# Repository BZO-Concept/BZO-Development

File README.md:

# BZO Concept – Development

Development boards and libraries designed by **BZO Concept** to test circuits in real conditions.
These boards are used during development and are shared, complete and working, so anyone can study, build or reuse them.
This repository mirrors the *Développement* section of [bzo-concept.fr](https://www.bzo-concept.fr/developpement/).

## Boards (KiCad projects, PDF schematics, production files)

| Folder | Description |
|---|---|
| [UART_UPDI_Dongle](UART_UPDI_Dongle) | USB–UART / UPDI dongle for programming and debugging, with quick access to 5V, 3V3 and GND rails |
| [AVR32DD32_DevBoard](AVR32DD32_DevBoard) | Nano-sized AVR32DD32 board: 24 MHz internal oscillator, 23 ADCs, DAC, MVIO. Arduino IDE + [DxCore](https://github.com/SpenceKonde/DxCore) |
| [BigBoard_STM32F405](BigBoard_STM32F405) | Large STM32F405RGT6 test board: every useful pin on headers with LED drivers. Used to validate pin assignment, serial, CAN and firmware on BZO ECUs. Arduino IDE + [Arduino Core STM32](https://github.com/stm32duino/Arduino_Core_STM32) |
| [STM32F042F6P7_DevBoard](STM32F042F6P7_DevBoard) | Small STM32F042F6P7 (TSSOP-20, 48 MHz) board with USB–UART, programmable from Arduino IDE. Arduino IDE + [Arduino Core STM32](https://github.com/stm32duino/Arduino_Core_STM32) |

## Libraries (Arduino IDE)

| Folder | Description |
|---|---|
| [BZO_PWM_Generator](BZO_PWM_Generator) | Software PWM on any pin of any processor (ATtiny, ATmega, STM32…), 1–1000 Hz, duty or frequency modulation, 4 independent channels, no dependency |
| [TunerStudio_Library](TunerStudio_Library) | Universal TunerStudio communication library (and any `.ini` based software) for configuration and monitoring of custom modules. Bluetooth tested (MSDroid). Example sketch and `.ini` included |

## See also

ECU firmware, datasheets and tools: [BZO-Downloads](https://github.com/BZO-Concept/BZO-Downloads)

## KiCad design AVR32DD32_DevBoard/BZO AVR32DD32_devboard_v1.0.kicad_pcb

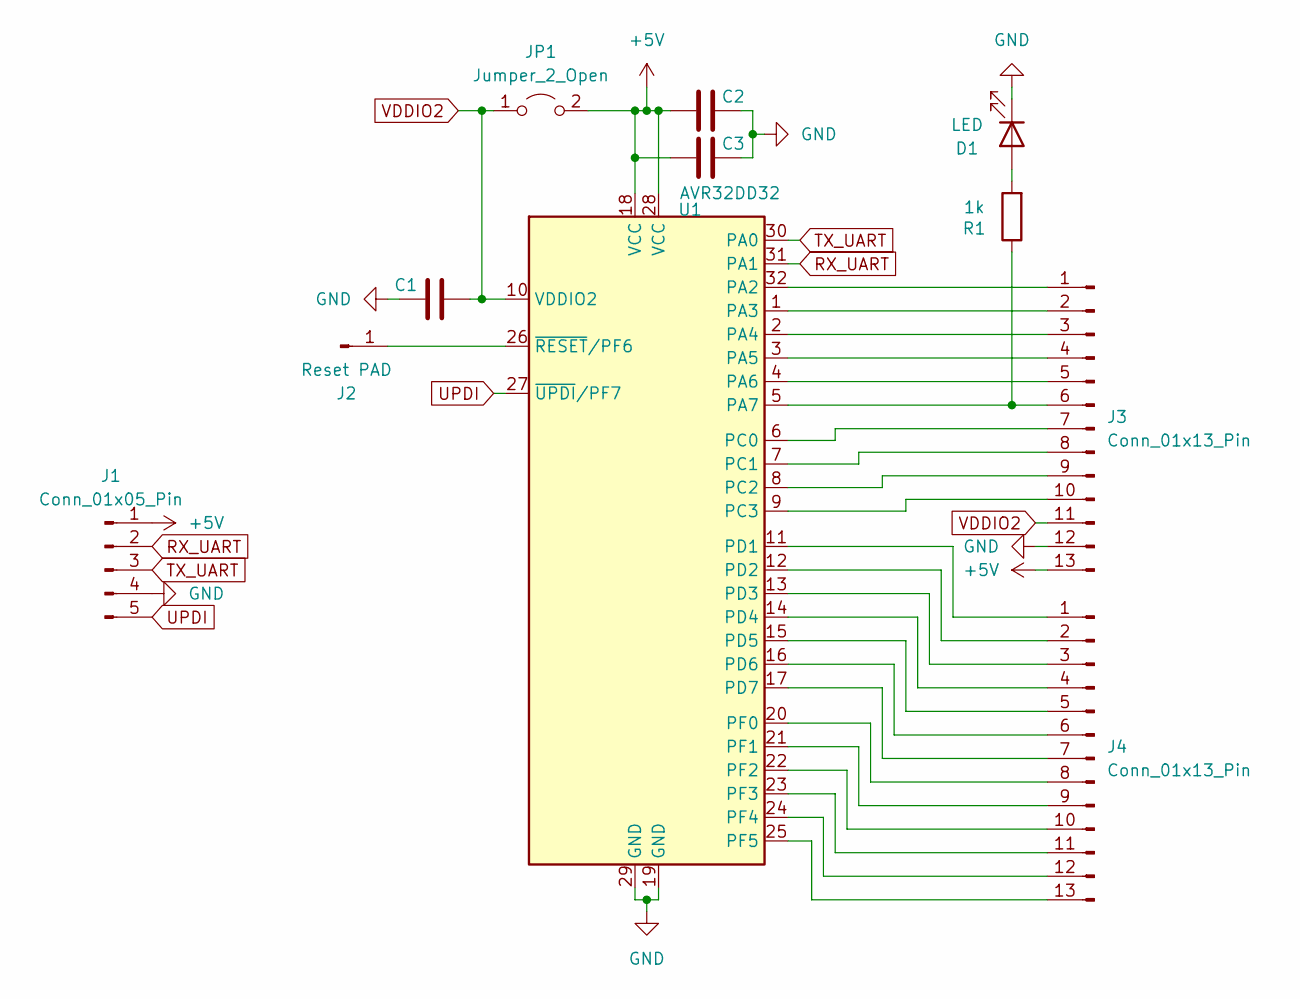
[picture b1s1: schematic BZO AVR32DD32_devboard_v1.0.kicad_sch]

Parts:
C1, C2, C3: 0.1uF; C_0805_2012Metric_Pad1.18x1.45mm_HandSolder; LCSC Part # C0805C104J5RACTU
D1: LED; LED_1206_3216Metric_Pad1.42x1.75mm_HandSolder(clean); LCSC Part # //////////////////////////
J1: Conn_01x05_Pin; PinHeader_1x05_P2.54mm_Vertical; LCSC Part # //////////////////////////
J2: Reset PAD; PinHeader_1x01_P1.00mm_Vertical; LCSC Part # //////////////////////////
J3, J4: Conn_01x13_Pin; PinHeader_1x13_P2.54mm_Vertical; LCSC Part # //////////////////////////
JP1: Jumper_2_Open; SolderJumper-2_P1.3mm_Open_RoundedPad1.0x1.5mm; LCSC Part # //////////////////////////
R1: 1k; R_0805_2012Metric_Pad1.20x1.40mm_HandSolder; LCSC Part # CR0805-FX-1001ELF
U1: AVR32DD32; TQFP-32_7x7mm_P0.8mm; LCSC Part # AVR32DD32

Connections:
+5V: C2.1, C3.1, J1.1, J3.13, JP1.2 (B), U1.18 (VCC), U1.28 (VCC)
GND: C1.1, C2.2, C3.2, D1.1 (K), J1.4, J3.12, U1.19 (GND), U1.29 (GND)
unnamed: D1.2 (A), R1.2
unnamed: J2.1, U1.26 (~RESET/PF6)
unnamed: J3.1, U1.32 (PA2)
unnamed: J3.2, U1.1 (PA3)
unnamed: J3.3, U1.2 (PA4)
unnamed: J3.4, U1.3 (PA5)
unnamed: J3.5, U1.4 (PA6)
unnamed: J3.6, R1.1, U1.5 (PA7)
unnamed: J3.7, U1.6 (PC0)
unnamed: J3.8, U1.7 (PC1)
unnamed: J3.9, U1.8 (PC2)
unnamed: J3.10, U1.9 (PC3)
unnamed: J4.1, U1.11 (PD1)
unnamed: J4.2, U1.12 (PD2)
unnamed: J4.3, U1.13 (PD3)
unnamed: J4.4, U1.14 (PD4)
unnamed: J4.5, U1.15 (PD5)
unnamed: J4.6, U1.16 (PD6)
unnamed: J4.7, U1.17 (PD7)
unnamed: J4.8, U1.20 (PF0)
unnamed: J4.9, U1.21 (PF1)
unnamed: J4.10, U1.22 (PF2)
unnamed: J4.11, U1.23 (PF3)
unnamed: J4.12, U1.24 (PF4)
unnamed: J4.13, U1.25 (PF5)
RX_UART: J1.2, U1.31 (PA1)
TX_UART: J1.3, U1.30 (PA0)
UPDI: J1.5, U1.27 (~UPDI/PF7)
VDDIO2: C1.2, J3.11, JP1.1 (A), U1.10 (VDDIO2)

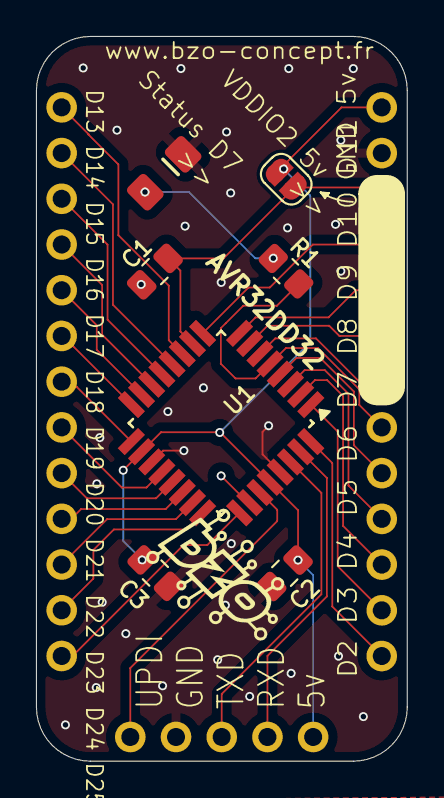
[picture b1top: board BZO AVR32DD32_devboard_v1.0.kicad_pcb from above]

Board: 2 copper layers, 20.6 x 40.3 mm, 11 parts (1 on the bottom side), 31 nets.

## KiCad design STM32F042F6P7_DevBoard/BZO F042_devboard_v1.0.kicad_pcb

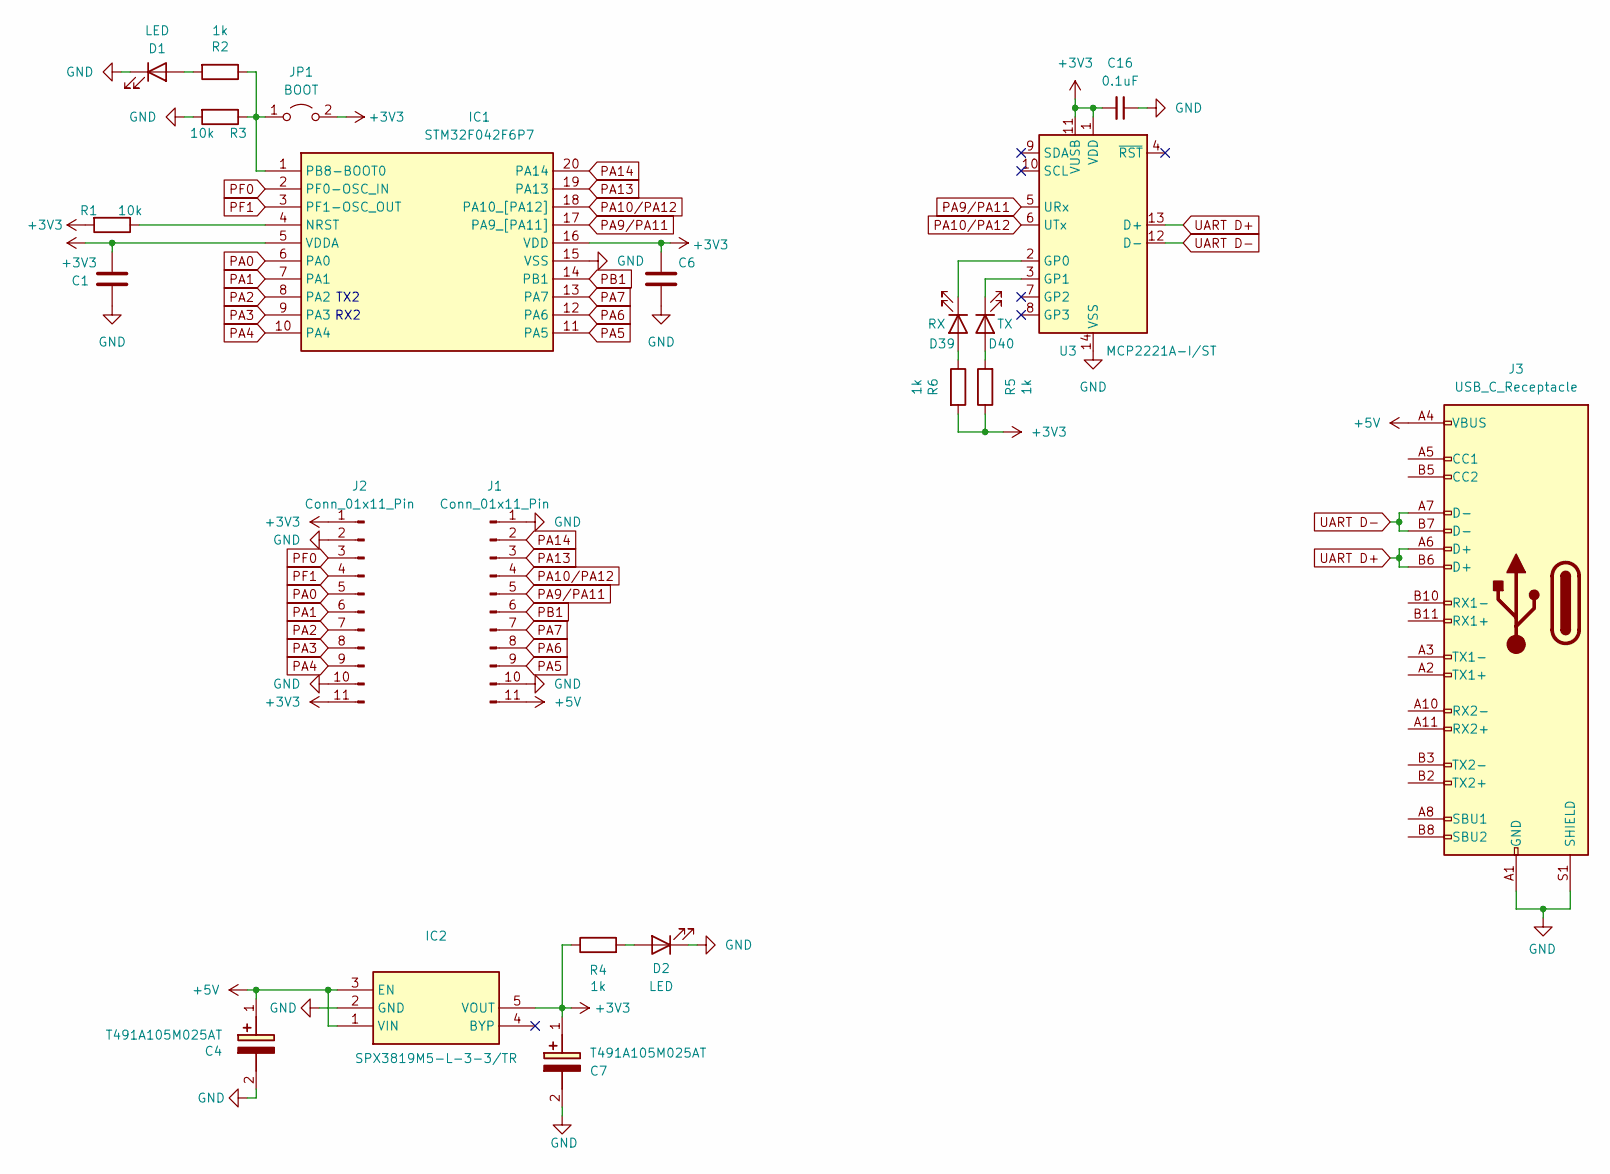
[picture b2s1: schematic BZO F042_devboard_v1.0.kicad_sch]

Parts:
C1, C6, C16: 0.1uF; C_0805_2012Metric_Pad1.18x1.45mm_HandSolder; LCSC Part # C0805C104J5RACTU
C4, C7: T491A105M025AT; T491A(clean); Mouser Part Number 80-T491A105M025
D1, D2: LED; LED_1206_3216Metric_Pad1.42x1.75mm_HandSolder(clean); LCSC Part # //////////////////////////
D39: RX; LED_1206_3216Metric_Pad1.42x1.75mm_HandSolder(clean); LCSC Part # //////////////////////////
D40: TX; LED_1206_3216Metric_Pad1.42x1.75mm_HandSolder(clean); LCSC Part # //////////////////////////
IC1: STM32F042F6P7; CLT34BT6; Mouser Part Number 511-STM32F042F6P7
IC2: SPX3819M5-L-3-3/TR; SOT95P280X145-5N; Mouser Part Number 701-SPX3819M5-L-50TR
J1, J2: Conn_01x11_Pin; PinHeader_1x11_P2.54mm_Vertical
J3: USB_C_Receptacle; USB_C_Receptacle_GCT_USB4085; LCSC Part # USB4085-GF-A
JP1: BOOT; SW_Push_SPST_NO_Alps_SKRK
R1, R3: 10k; R_0805_2012Metric_Pad1.20x1.40mm_HandSolder; LCSC Part # CR0805-FX-1002ELF
R2, R4, R5, R6: 1k; R_0805_2012Metric_Pad1.20x1.40mm_HandSolder; LCSC Part # CR0805-FX-1001ELF
U3: MCP2221A-I/ST; TSSOP-14_4.4x5mm_P0.65mm; LCSC Part # MCP2221A-I/ST

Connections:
+3V3: C1.1, C6.1, C7.1 (+), C16.2, IC1.5 (VDDA), IC1.16 (VDD), IC2.5 (VOUT), J2.1, J2.11, JP1.2 (B), R1.2, R4.1, R5.1, R6.2, U3.1 (VDD), U3.11 (VUSB)
+5V: C4.1 (+), IC2.1 (VIN), IC2.3 (EN), J1.11, J3.A4 (VBUS), J3.A9 (VBUS), J3.B4 (VBUS), J3.B9 (VBUS)
GND: C1.2, C4.2 (-), C6.2, C7.2 (-), C16.1, D1.1 (K), D2.1 (K), IC1.15 (VSS), IC2.2 (GND), J1.1, J1.10, J2.2, J2.10, J3.A1 (GND), J3.A12 (GND), J3.B1 (GND), J3.B12 (GND), J3.S1 (SHIELD), R3.2, U3.14 (VSS)
unnamed: D1.2 (A), R2.2
unnamed: D2.2 (A), R4.2
unnamed: D39.2 (A), R6.1
unnamed: D39.1 (K), U3.2 (GP0)
unnamed: D40.2 (A), R5.2
unnamed: D40.1 (K), U3.3 (GP1)
unnamed: IC1.4 (NRST), R1.1
unnamed: IC1.1 (PB8-BOOT0), JP1.1 (A), R2.1, R3.1
PA0: IC1.6 (PA0), J2.5
PA1: IC1.7 (PA1), J2.6
PA2: IC1.8 (PA2), J2.7
PA3: IC1.9 (PA3), J2.8
PA4: IC1.10 (PA4), J2.9
PA5: IC1.11 (PA5), J1.9
PA6: IC1.12 (PA6), J1.8
PA7: IC1.13 (PA7), J1.7
PA9/PA11: IC1.17 (PA9_[PA11]), J1.5, U3.5 (URx)
PA10/PA12: IC1.18 (PA10_[PA12]), J1.4, U3.6 (UTx)
PA13: IC1.19 (PA13), J1.3
PA14: IC1.20 (PA14), J1.2
PB1: IC1.14 (PB1), J1.6
PF0: IC1.2 (PF0-OSC_IN), J2.3
PF1: IC1.3 (PF1-OSC_OUT), J2.4
UART D+: J3.A6 (D+), J3.B6 (D+), U3.13 (D+)
UART D-: J3.A7 (D-), J3.B7 (D-), U3.12 (D-)

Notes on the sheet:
TX2
RX2

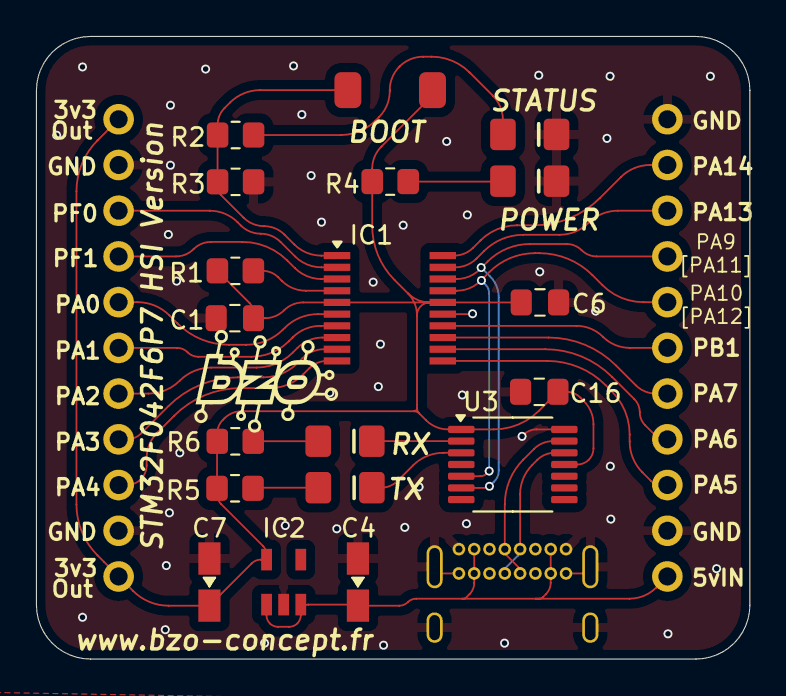
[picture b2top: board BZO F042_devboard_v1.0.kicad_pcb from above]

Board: 2 copper layers, 39.6 x 34.6 mm, 22 parts (0 on the bottom side), 28 nets.

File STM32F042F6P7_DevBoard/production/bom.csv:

Designator,Footprint,Quantity,Value,LCSC Part #
"C1, C16, C6",0805,3,0.1uF,C0805C104J5RACTU
"C4, C7",T491A(clean),2,T491A105M025AT,
"D1, D2",1206,2,LED,//////////////////////////
D39,1206,1,RX,//////////////////////////
D40,1206,1,TX,//////////////////////////
IC1,CLT34BT6,1,STM32F042F6P7,
IC2,SOT95P280X145-5N,1,SPX3819M5-L-3-3/TR,
"J1, J2",PinHeader_1x11_P2.54mm_Vertical,2,Conn_01x11_Pin,
J3,USB_C_Receptacle_GCT_USB4085,1,USB_C_Receptacle,USB4085-GF-A
JP1,SW_Push_SPST_NO_Alps_SKRK,1,BOOT,
"R1, R3",0805,2,10k,CR0805-FX-1002ELF
"R2, R4, R5, R6",0805,4,1k,CR0805-FX-1001ELF
U3,TSSOP-14_4.4x5mm_P0.65mm,1,MCP2221A-I/ST,MCP2221A-I/ST

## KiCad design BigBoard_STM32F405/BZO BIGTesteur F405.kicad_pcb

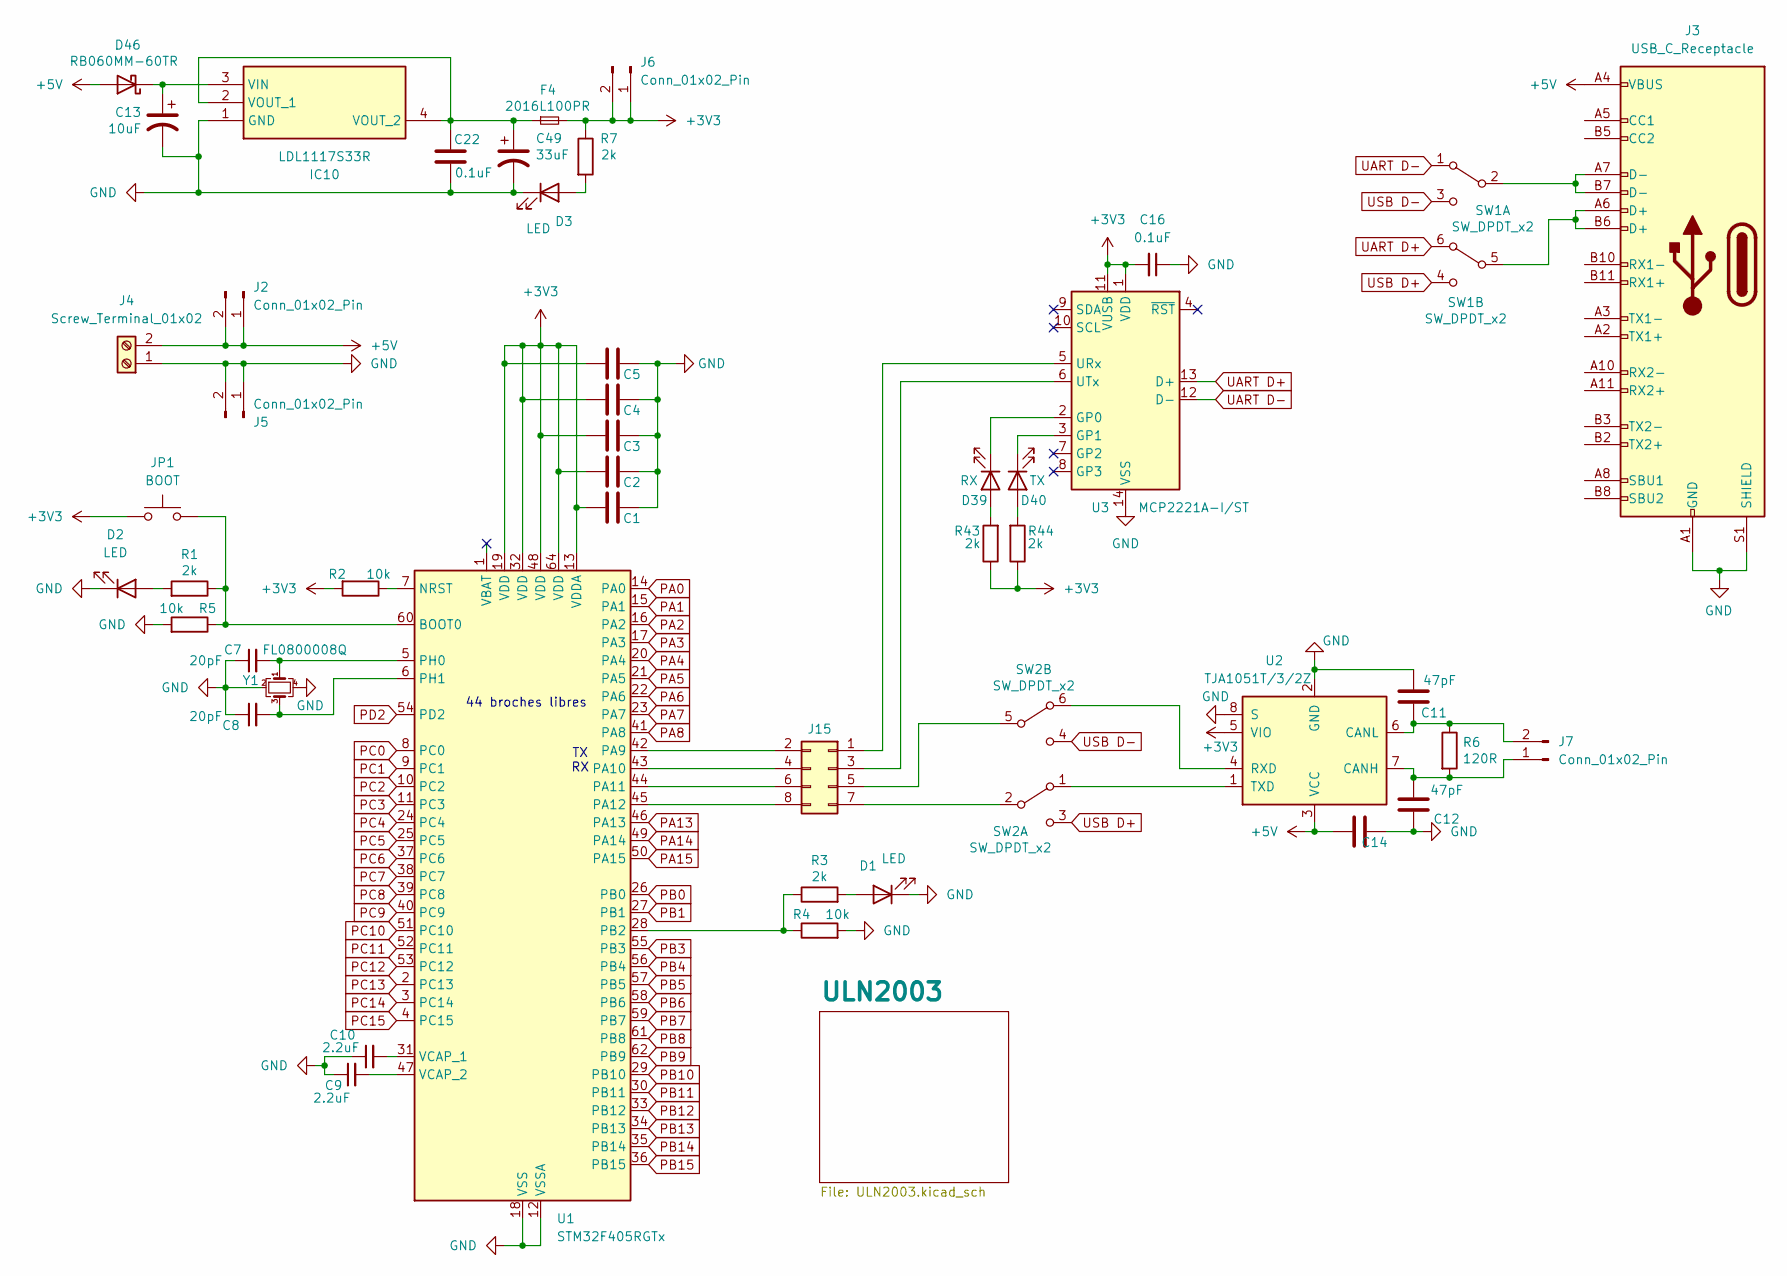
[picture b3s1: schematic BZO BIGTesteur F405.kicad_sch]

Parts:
C1, C2, C3, C4, C5, C14, C16, C22: 0.1uF; C_0805_2012Metric_Pad1.18x1.45mm_HandSolder; LCSC Part # C0805C104J5RACTU
C7, C8: 20pF; C_0805_2012Metric_Pad1.18x1.45mm_HandSolder; LCSC Part # C0805C200J5HACTU
C9, C10: 2.2uF; C_0805_2012Metric_Pad1.18x1.45mm_HandSolder; LCSC Part # C0805C225J4REC7210
C11, C12: 47pF; C_0805_2012Metric_Pad1.18x1.45mm_HandSolder; LCSC Part # C0805C470J5GACTU
C13: 10uF; CP_EIA-6032-28_Kemet-C_Pad2.25x2.35mm_HandSolder; LCSC Part # T491C106K035ATAUTO
C49: 33uF; CP_EIA-3528-21_Kemet-B_Pad1.50x2.35mm_HandSolder; LCSC Part # T491B336K016ATAUTO
D1, D2, D3: LED; LED_1206_3216Metric_ReverseMount; LCSC Part # //////////////////////////
D39: RX; LED_1206_3216Metric_ReverseMount; LCSC Part # //////////////////////////
D40: TX; LED_1206_3216Metric_ReverseMount; LCSC Part # //////////////////////////
D46: RB060MM-60TR; LED_1206_3216Metric_Pad1.42x1.75mm_HandSolder(clean); Mouser Part Number 755-RB060MM-60TR
F4: 2016L100PR; FUSC5141X160N; LCSC Part # 2016L100PR
IC10: LDL1117S33R; SOT230P700X180-4N; Mouser Part Number 511-LDL1117S33R
J2, J5, J6, J7: Conn_01x02_Pin; PinHeader_2x01_P2.54mm_Vertical; LCSC Part # //////////////////////////
J3: USB_C_Receptacle; USB_C_Receptacle_GCT_USB4085; LCSC Part # USB4085-GF-A
J4: Screw_Terminal_01x02; TerminalBlock_bornier-2_P5.08mm; LCSC Part # //////////////////////////
J15: Conn_02x04_Counter_Clockwise; PinHeader_2x04_P2.54mm_Vertical; LCSC Part # //////////////////////////
JP1: BOOT; SW_Push_SPST_NO_Alps_SKRK; LCSC Part # //////////////////////////
R1, R3, R7, R43, R44: 2k; R_0805_2012Metric_Pad1.20x1.40mm_HandSolder; LCSC Part # CR0805-FX-2001ELF
R2, R4, R5: 10k; R_0805_2012Metric_Pad1.20x1.40mm_HandSolder; LCSC Part # CR0805-FX-1002ELF
R6: 120R; R_0805_2012Metric_Pad1.20x1.40mm_HandSolder; LCSC Part # CR0805-FX-1200ELF
SW1, SW2: SW_DPDT_x2; SMDIP-6_W7.62mm; LCSC Part # //////////////////////////
U1: STM32F405RGTx; LQFP-64_10x10mm_P0.5mm; LCSC Part # STM32F405RGTx
U2: TJA1051T/3/2Z; SOIC-8_3.9x4.9mm_P1.27mm; LCSC Part # TJA1051T/3/2Z
U3: MCP2221A-I/ST; TSSOP-14_4.4x5mm_P0.65mm; LCSC Part # MCP2221A-I/ST
Y1: FL0800008Q; Mouser Part Number 729-FL0800008Q

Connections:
+3V3: C1.1, C2.1, C3.1, C4.1, C5.1, C16.2, F4.2, J6.1, J6.2, JP1.1, R2.2, R7.1, R43.1, R44.1, U1.13 (VDDA), U1.19 (VDD), U1.32 (VDD), U1.48 (VDD), U1.64 (VDD), U2.5 (VIO), U3.1 (VDD), U3.11 (VUSB); also elsewhere on the board
+5V: C14.1, D46.2 (A), J2.1, J2.2, J3.A4 (VBUS), J3.A9 (VBUS), J3.B4 (VBUS), J3.B9 (VBUS), J4.2, U2.3 (VCC)
GND: C1.2, C2.2, C3.2, C4.2, C5.2, C7.1, C8.1, C9.1, C10.1, C11.1, C12.2, C13.2, C14.2, C16.1, C22.2, C49.2, D1.1 (K), D2.1 (K), D3.1 (K), IC10.1 (GND), J3.A1 (GND), J3.A12 (GND), J3.B1 (GND), J3.B12 (GND), J3.S1 (SHIELD), J4.1, J5.1, J5.2, R4.2, R5.2, U1.12 (VSSA), U1.18 (VSS), U1.63 (VSS), U2.2 (GND), U2.8 (S), U3.14 (VSS), Y1.2, Y1.4; also elsewhere on the board
unnamed: D1.2 (A), R3.2
unnamed: D2.2 (A), R1.2
unnamed: D3.2 (A), R7.2
unnamed: D39.2 (A), R43.2
unnamed: D39.1 (K), U3.2 (GP0)
unnamed: D40.2 (A), R44.2
unnamed: D40.1 (K), U3.3 (GP1)
unnamed: C13.1, D46.1 (K), IC10.3 (VIN)
unnamed: C22.1, C49.1, F4.1, IC10.2 (VOUT_1), IC10.4 (VOUT_2)
unnamed: C12.1, J7.1, R6.2, U2.7 (CANH)
unnamed: C11.2, J7.2, R6.1, U2.6 (CANL)
unnamed: J15.1, U3.5 (URx)
unnamed: J15.2, U1.42 (PA9)
unnamed: J15.3, U3.6 (UTx)
unnamed: J15.4, U1.43 (PA10)
unnamed: J15.5, SW2.5 (B)
unnamed: J15.6, U1.44 (PA11)
unnamed: J15.7, SW2.2 (B)
unnamed: J15.8, U1.45 (PA12)
unnamed: J3.A7 (D-), J3.B7 (D-), SW1.2 (B)
unnamed: J3.A6 (D+), J3.B6 (D+), SW1.5 (B)
unnamed: SW2.1 (A), U2.1 (TXD)
unnamed: SW2.6 (A), U2.4 (RXD)
unnamed: JP1.2, R1.1, R5.1, U1.60 (BOOT0)
unnamed: R2.1, U1.7 (NRST)
unnamed: R3.1, R4.1, U1.28 (PB2)
unnamed: C7.2, U1.5 (PH0), Y1.1
unnamed: C8.2, U1.6 (PH1), Y1.3
unnamed: C10.2, U1.31 (VCAP_1)
unnamed: C9.2, U1.47 (VCAP_2)
PA0: U1.14 (PA0); also elsewhere on the board
PA1: U1.15 (PA1); also elsewhere on the board
PA2: U1.16 (PA2); also elsewhere on the board
PA3: U1.17 (PA3); also elsewhere on the board
PA4: U1.20 (PA4); also elsewhere on the board
PA5: U1.21 (PA5); also elsewhere on the board
PA6: U1.22 (PA6); also elsewhere on the board
PA7: U1.23 (PA7); also elsewhere on the board
PA8: U1.41 (PA8); also elsewhere on the board
PA13: U1.46 (PA13); also elsewhere on the board
PA14: U1.49 (PA14); also elsewhere on the board
PA15: U1.50 (PA15); also elsewhere on the board
PB0: U1.26 (PB0); also elsewhere on the board
PB1: U1.27 (PB1); also elsewhere on the board
PB3: U1.55 (PB3); also elsewhere on the board
PB4: U1.56 (PB4); also elsewhere on the board
PB5: U1.57 (PB5); also elsewhere on the board
PB6: U1.58 (PB6); also elsewhere on the board
PB7: U1.59 (PB7); also elsewhere on the board
PB8: U1.61 (PB8); also elsewhere on the board
PB9: U1.62 (PB9); also elsewhere on the board
PB10: U1.29 (PB10); also elsewhere on the board
PB11: U1.30 (PB11); also elsewhere on the board
PB12: U1.33 (PB12); also elsewhere on the board
PB13: U1.34 (PB13); also elsewhere on the board
PB14: U1.35 (PB14); also elsewhere on the board
PB15: U1.36 (PB15); also elsewhere on the board
PC0: U1.8 (PC0); also elsewhere on the board
PC1: U1.9 (PC1); also elsewhere on the board
PC2: U1.10 (PC2); also elsewhere on the board
PC3: U1.11 (PC3); also elsewhere on the board
PC4: U1.24 (PC4); also elsewhere on the board
PC5: U1.25 (PC5); also elsewhere on the board
PC6: U1.37 (PC6); also elsewhere on the board
PC7: U1.38 (PC7); also elsewhere on the board
PC8: U1.39 (PC8); also elsewhere on the board
PC9: U1.40 (PC9); also elsewhere on the board
PC10: U1.51 (PC10); also elsewhere on the board
PC11: U1.52 (PC11); also elsewhere on the board
PC12: U1.53 (PC12); also elsewhere on the board
PC13: U1.2 (PC13); also elsewhere on the board
PC14: U1.3 (PC14); also elsewhere on the board
PC15: U1.4 (PC15); also elsewhere on the board
PD2: U1.54 (PD2); also elsewhere on the board
UART D+: SW1.6 (A), U3.13 (D+)
UART D-: SW1.1 (A), U3.12 (D-)
USB D+: SW1.4 (C), SW2.3 (C)
USB D-: SW1.3 (C), SW2.4 (C)

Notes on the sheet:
TX RX
44 broches libres

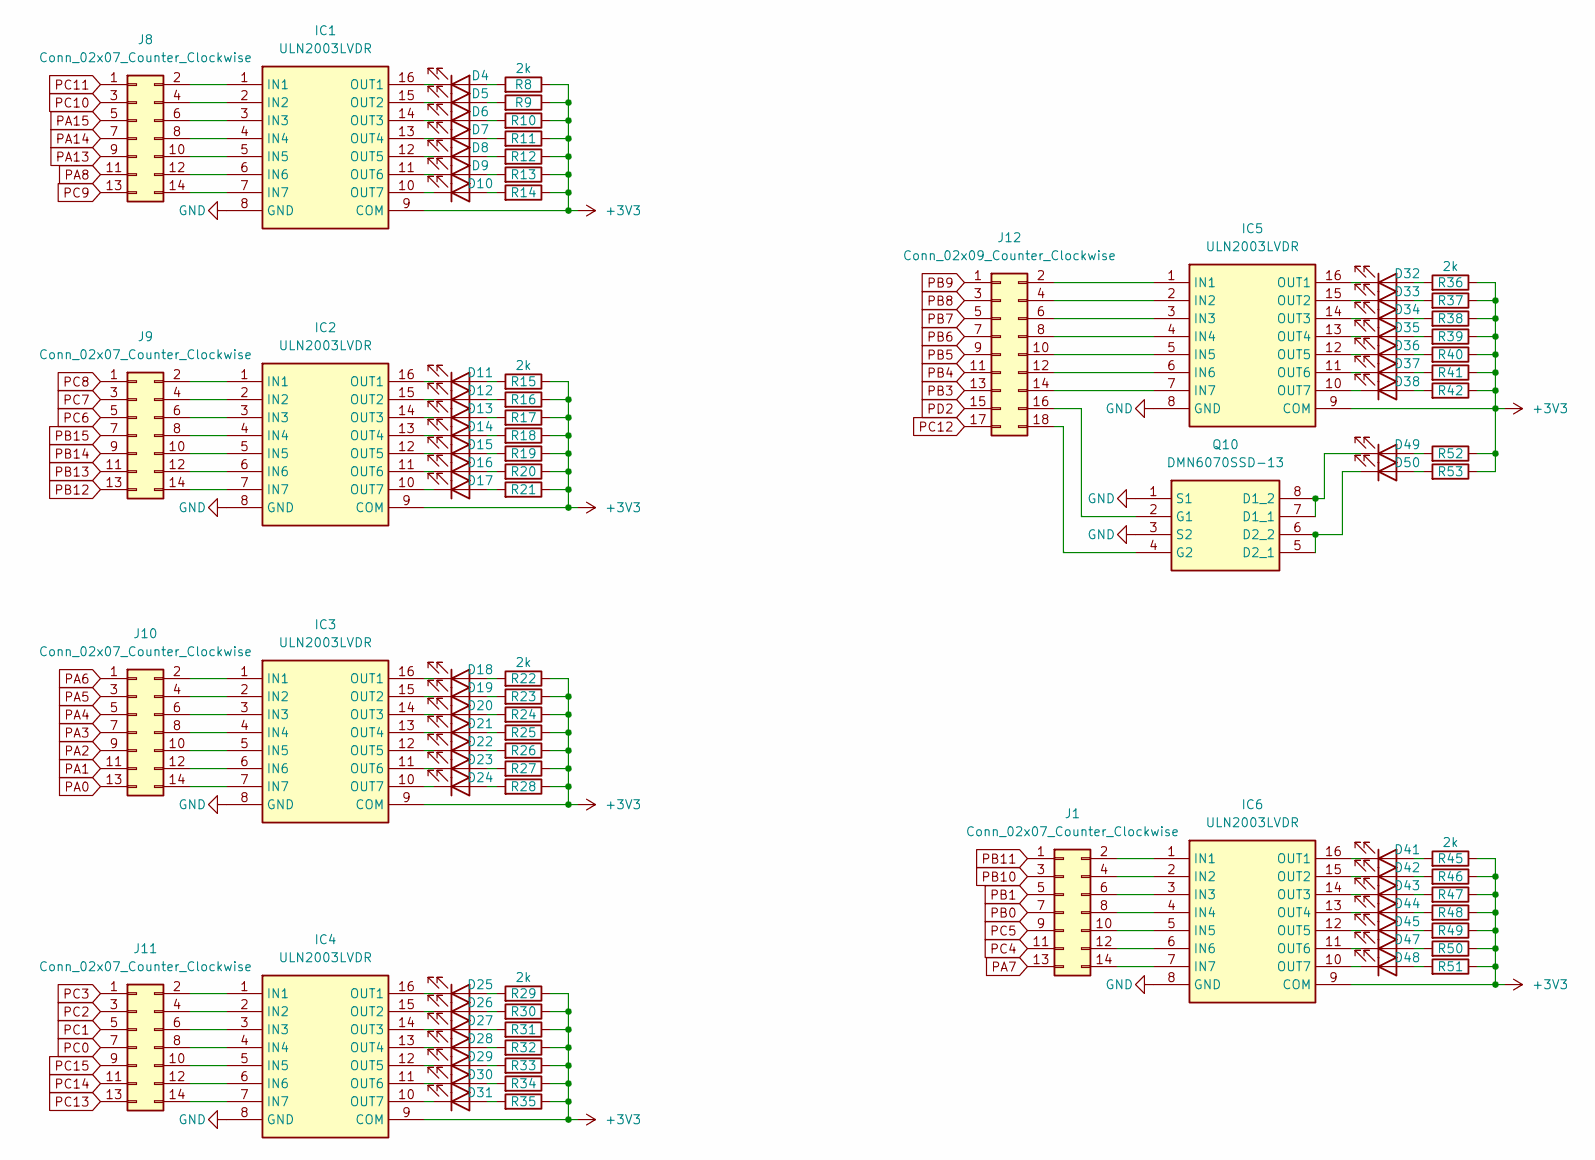
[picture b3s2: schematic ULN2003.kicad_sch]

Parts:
D4, D5, D6, D7, D8, D9, D10, D11, D12, D13, D14, D15, D16, D17, D18, D19, D20, D21, D22, D23, D24, D25, D26, D27, D28, D29, D30, D31, D32, D33, D34, D35, D36, D37, D38, D41, D42, D43, D44, D45, D47, D48, D49, D50: LED; LED_1206_3216Metric_ReverseMount; LCSC Part # //////////////////////////
IC1, IC2, IC3, IC4, IC5, IC6: ULN2003LVDR; SOIC127P600X175-16N; Mouser Part Number 595-ULN2003LVDR
J1, J8, J9, J10, J11: Conn_02x07_Counter_Clockwise; PinHeader_2x07_P2.54mm_Vertical; LCSC Part # //////////////////////////
J12: Conn_02x09_Counter_Clockwise; PinHeader_2x09_P2.54mm_Vertical; LCSC Part # //////////////////////////
Q10: DMN6070SSD-13; SOIC127P600X175-8N; Mouser Part Number 621-DMN6070SSD-13
R8, R9, R10, R11, R12, R13, R14, R15, R16, R17, R18, R19, R20, R21, R22, R23, R24, R25, R26, R27, R28, R29, R30, R31, R32, R33, R34, R35, R36, R37, R38, R39, R40, R41, R42, R45, R46, R47, R48, R49, R50, R51, R52, R53: 2k; R_0805_2012Metric_Pad1.20x1.40mm_HandSolder; LCSC Part # CR0805-FX-2001ELF

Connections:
+3V3: IC1.9 (COM), IC2.9 (COM), IC3.9 (COM), IC4.9 (COM), IC5.9 (COM), IC6.9 (COM), R8.1, R9.1, R10.1, R11.1, R12.1, R13.1, R14.1, R15.1, R16.1, R17.1, R18.1, R19.1, R20.1, R21.1, R22.1, R23.1, R24.1, R25.1, R26.1, R27.1, R28.1, R29.1, R30.1, R31.1, R32.1, R33.1, R34.1, R35.1, R36.1, R37.1, R38.1, R39.1, R40.1, R41.1, R42.1, R45.1, R46.1, R47.1, R48.1, R49.1, R50.1, R51.1, R52.1, R53.1; also elsewhere on the board
GND: IC1.8 (GND), IC2.8 (GND), IC3.8 (GND), IC4.8 (GND), IC5.8 (GND), IC6.8 (GND), Q10.1 (S1), Q10.3 (S2); also elsewhere on the board
unnamed: D4.2 (A), R8.2
unnamed: D4.1 (K), IC1.16 (OUT1)
unnamed: D5.2 (A), R9.2
unnamed: D5.1 (K), IC1.15 (OUT2)
unnamed: D6.2 (A), R10.2
unnamed: D6.1 (K), IC1.14 (OUT3)
unnamed: D7.2 (A), R11.2
unnamed: D7.1 (K), IC1.13 (OUT4)
unnamed: D8.2 (A), R12.2
unnamed: D8.1 (K), IC1.12 (OUT5)
unnamed: D9.2 (A), R13.2
unnamed: D9.1 (K), IC1.11 (OUT6)
unnamed: D10.2 (A), R14.2
unnamed: D10.1 (K), IC1.10 (OUT7)
unnamed: D11.2 (A), R15.2
unnamed: D11.1 (K), IC2.16 (OUT1)
unnamed: D12.2 (A), R16.2
unnamed: D12.1 (K), IC2.15 (OUT2)
unnamed: D13.2 (A), R17.2
unnamed: D13.1 (K), IC2.14 (OUT3)
unnamed: D14.2 (A), R18.2
unnamed: D14.1 (K), IC2.13 (OUT4)
unnamed: D15.2 (A), R19.2
unnamed: D15.1 (K), IC2.12 (OUT5)
unnamed: D16.2 (A), R20.2
unnamed: D16.1 (K), IC2.11 (OUT6)
unnamed: D17.2 (A), R21.2
unnamed: D17.1 (K), IC2.10 (OUT7)
unnamed: D18.2 (A), R22.2
unnamed: D18.1 (K), IC3.16 (OUT1)
unnamed: D19.2 (A), R23.2
unnamed: D19.1 (K), IC3.15 (OUT2)
unnamed: D20.2 (A), R24.2
unnamed: D20.1 (K), IC3.14 (OUT3)
unnamed: D21.2 (A), R25.2
unnamed: D21.1 (K), IC3.13 (OUT4)
unnamed: D22.2 (A), R26.2
unnamed: D22.1 (K), IC3.12 (OUT5)
unnamed: D23.2 (A), R27.2
unnamed: D23.1 (K), IC3.11 (OUT6)
unnamed: D24.2 (A), R28.2
unnamed: D24.1 (K), IC3.10 (OUT7)
unnamed: D25.2 (A), R29.2
unnamed: D25.1 (K), IC4.16 (OUT1)
unnamed: D26.2 (A), R30.2
unnamed: D26.1 (K), IC4.15 (OUT2)
unnamed: D27.2 (A), R31.2
unnamed: D27.1 (K), IC4.14 (OUT3)
unnamed: D28.2 (A), R32.2
unnamed: D28.1 (K), IC4.13 (OUT4)
unnamed: D29.2 (A), R33.2
unnamed: D29.1 (K), IC4.12 (OUT5)
unnamed: D30.2 (A), R34.2
unnamed: D30.1 (K), IC4.11 (OUT6)
unnamed: D31.2 (A), R35.2
unnamed: D31.1 (K), IC4.10 (OUT7)
unnamed: D32.2 (A), R36.2
unnamed: D32.1 (K), IC5.16 (OUT1)
unnamed: D33.2 (A), R37.2
unnamed: D33.1 (K), IC5.15 (OUT2)
unnamed: D34.2 (A), R38.2
unnamed: D34.1 (K), IC5.14 (OUT3)
unnamed: D35.2 (A), R39.2
unnamed: D35.1 (K), IC5.13 (OUT4)
unnamed: D36.2 (A), R40.2
unnamed: D36.1 (K), IC5.12 (OUT5)
unnamed: D37.2 (A), R41.2
unnamed: D37.1 (K), IC5.11 (OUT6)
unnamed: D38.2 (A), R42.2
unnamed: D38.1 (K), IC5.10 (OUT7)
unnamed: D41.2 (A), R45.2
unnamed: D41.1 (K), IC6.16 (OUT1)
unnamed: D42.2 (A), R46.2
unnamed: D42.1 (K), IC6.15 (OUT2)
unnamed: D43.2 (A), R47.2
unnamed: D43.1 (K), IC6.14 (OUT3)
unnamed: D44.2 (A), R48.2
unnamed: D44.1 (K), IC6.13 (OUT4)
unnamed: D45.2 (A), R49.2
unnamed: D45.1 (K), IC6.12 (OUT5)
unnamed: D47.2 (A), R50.2
unnamed: D47.1 (K), IC6.11 (OUT6)
unnamed: D48.2 (A), R51.2
unnamed: D48.1 (K), IC6.10 (OUT7)
unnamed: D49.2 (A), R52.2
unnamed: D49.1 (K), Q10.7 (D1_1), Q10.8 (D1_2)
unnamed: D50.2 (A), R53.2
unnamed: D50.1 (K), Q10.5 (D2_1), Q10.6 (D2_2)
unnamed: IC1.1 (IN1), J8.2
unnamed: IC1.2 (IN2), J8.4
unnamed: IC1.3 (IN3), J8.6
unnamed: IC1.4 (IN4), J8.8
unnamed: IC1.5 (IN5), J8.10
unnamed: IC1.6 (IN6), J8.12
unnamed: IC1.7 (IN7), J8.14
unnamed: IC2.1 (IN1), J9.2
unnamed: IC2.2 (IN2), J9.4
unnamed: IC2.3 (IN3), J9.6
unnamed: IC2.4 (IN4), J9.8
unnamed: IC2.5 (IN5), J9.10
unnamed: IC2.6 (IN6), J9.12
unnamed: IC2.7 (IN7), J9.14
unnamed: IC3.1 (IN1), J10.2
unnamed: IC3.2 (IN2), J10.4
unnamed: IC3.3 (IN3), J10.6
unnamed: IC3.4 (IN4), J10.8
unnamed: IC3.5 (IN5), J10.10
unnamed: IC3.6 (IN6), J10.12
unnamed: IC3.7 (IN7), J10.14
unnamed: IC4.1 (IN1), J11.2
unnamed: IC4.2 (IN2), J11.4
unnamed: IC4.3 (IN3), J11.6
unnamed: IC4.4 (IN4), J11.8
unnamed: IC4.5 (IN5), J11.10
unnamed: IC4.6 (IN6), J11.12
unnamed: IC4.7 (IN7), J11.14
unnamed: IC5.1 (IN1), J12.2
unnamed: IC5.2 (IN2), J12.4
unnamed: IC5.3 (IN3), J12.6
unnamed: IC5.4 (IN4), J12.8
unnamed: IC5.5 (IN5), J12.10
unnamed: IC5.6 (IN6), J12.12
unnamed: IC5.7 (IN7), J12.14
unnamed: IC6.1 (IN1), J1.2
unnamed: IC6.2 (IN2), J1.4
unnamed: IC6.3 (IN3), J1.6
unnamed: IC6.4 (IN4), J1.8
unnamed: IC6.5 (IN5), J1.10
unnamed: IC6.6 (IN6), J1.12
unnamed: IC6.7 (IN7), J1.14
unnamed: J12.16, Q10.2 (G1)
unnamed: J12.18, Q10.4 (G2)
PA0: J10.13; also elsewhere on the board
PA1: J10.11; also elsewhere on the board
PA2: J10.9; also elsewhere on the board
PA3: J10.7; also elsewhere on the board
PA4: J10.5; also elsewhere on the board
PA5: J10.3; also elsewhere on the board
PA6: J10.1; also elsewhere on the board
PA7: J1.13; also elsewhere on the board
PA8: J8.11; also elsewhere on the board
PA13: J8.9; also elsewhere on the board
PA14: J8.7; also elsewhere on the board
PA15: J8.5; also elsewhere on the board
PB0: J1.7; also elsewhere on the board
PB1: J1.5; also elsewhere on the board
PB3: J12.13; also elsewhere on the board
PB4: J12.11; also elsewhere on the board
PB5: J12.9; also elsewhere on the board
PB6: J12.7; also elsewhere on the board
PB7: J12.5; also elsewhere on the board
PB8: J12.3; also elsewhere on the board
PB9: J12.1; also elsewhere on the board
PB10: J1.3; also elsewhere on the board
PB11: J1.1; also elsewhere on the board
PB12: J9.13; also elsewhere on the board
PB13: J9.11; also elsewhere on the board
PB14: J9.9; also elsewhere on the board
PB15: J9.7; also elsewhere on the board
PC0: J11.7; also elsewhere on the board
PC1: J11.5; also elsewhere on the board
PC2: J11.3; also elsewhere on the board
PC3: J11.1; also elsewhere on the board
PC4: J1.11; also elsewhere on the board
PC5: J1.9; also elsewhere on the board
PC6: J9.5; also elsewhere on the board
PC7: J9.3; also elsewhere on the board
PC8: J9.1; also elsewhere on the board
PC9: J8.13; also elsewhere on the board
PC10: J8.3; also elsewhere on the board
PC11: J8.1; also elsewhere on the board
PC12: J12.17; also elsewhere on the board
PC13: J11.13; also elsewhere on the board
PC14: J11.11; also elsewhere on the board
PC15: J11.9; also elsewhere on the board
PD2: J12.15; also elsewhere on the board

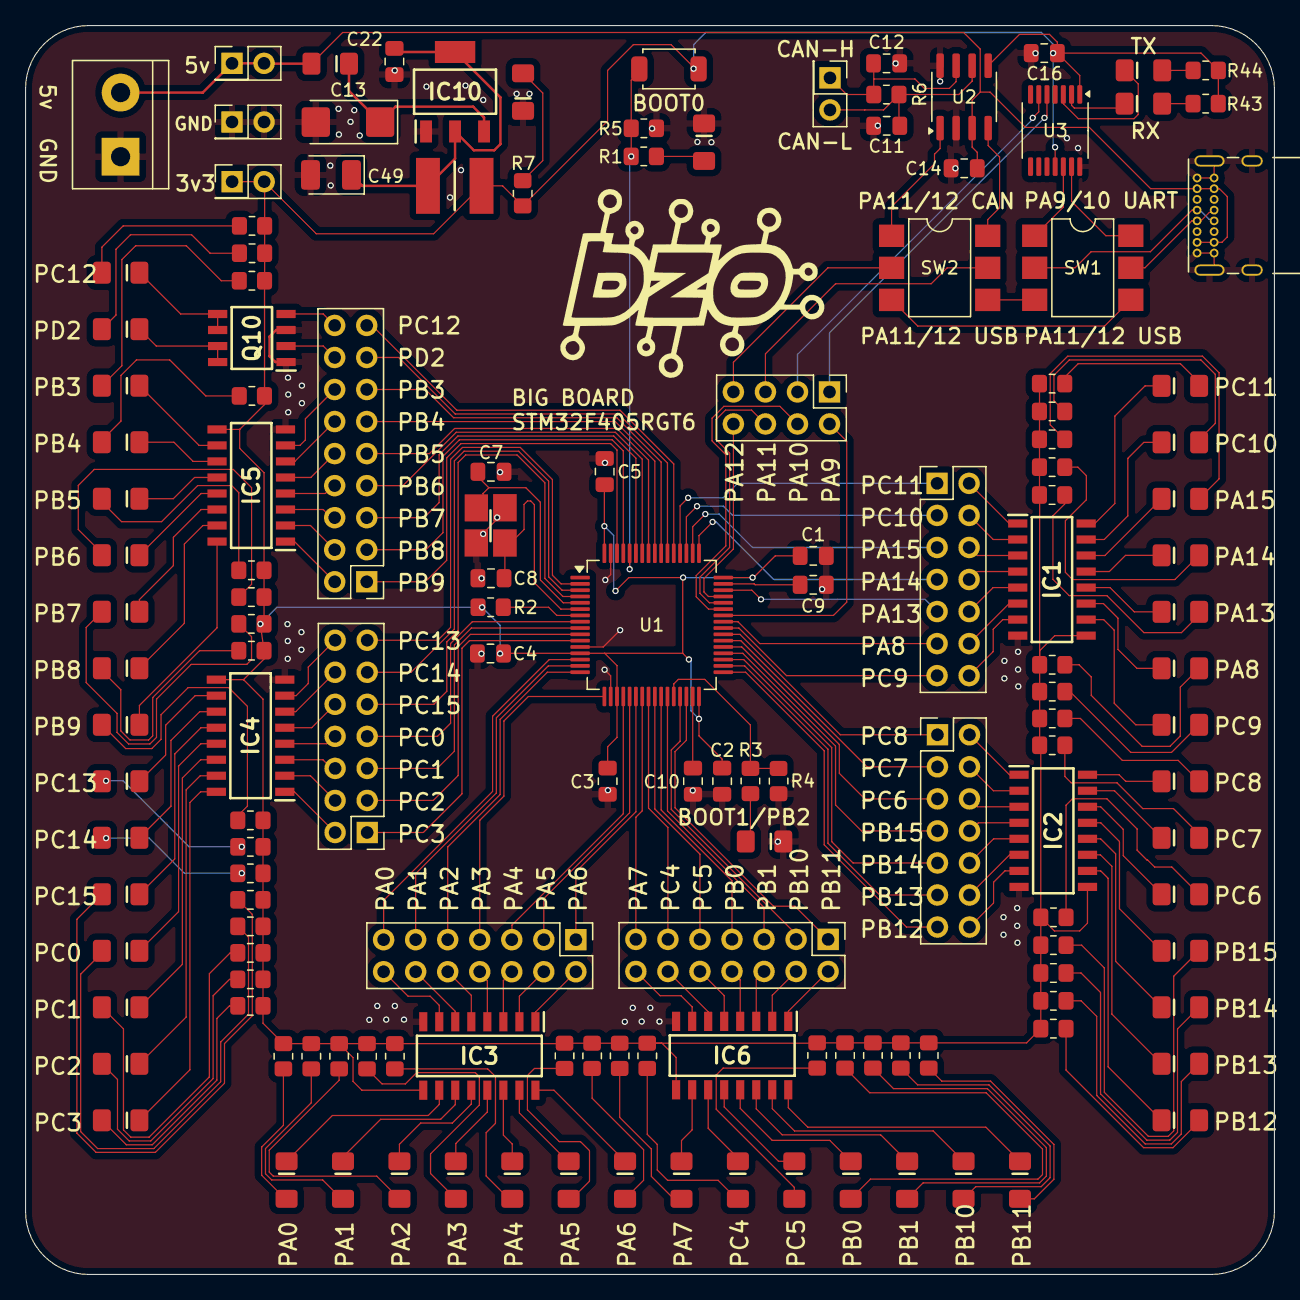
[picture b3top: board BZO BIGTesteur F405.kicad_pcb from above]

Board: 2 copper layers, 99.0 x 99.0 mm, 148 parts (0 on the bottom side), 213 nets.

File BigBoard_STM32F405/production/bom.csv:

Designator,Footprint,Quantity,Value,LCSC Part #
"C1, C14, C16, C2, C22, C3, C4, C5",0805,8,0.1uF,C0805C104J5RACTU
"C10, C9",0805,2,2.2uF,C0805C225J4REC7210 
"C11, C12",0805,2,47pF,C0805C470J5GACTU
C13,CP_EIA-6032-28_Kemet-C_Pad2.25x2.35mm_HandSolder,1,10uF,T491C106K035ATAUTO
C49,CP_EIA-3528-21_Kemet-B_Pad1.50x2.35mm_HandSolder,1,33uF,T491B336K016ATAUTO 
"C7, C8",0805,2,20pF,C0805C200J5HACTU
"D1, D10, D11, D12, D13, D14, D15, D16, D17, D18, D19, D2, D20, D21, D22, D23, D24, D25, D26, D27, D28, D29, D3, D30, D31, D32, D33, D34, D35, D36, D37, D38, D4, D41, D42, D43, D44, D45, D47, D48, D49, D5, D50, D6, D7, D8, D9",1206,47,LED,//////////////////////////
D39,1206,1,RX,//////////////////////////
D40,1206,1,TX,//////////////////////////
D46,1206,1,RB060MM-60TR,RB060MM-60TR
F4,FUSC5141X160N,1,2016L100PR,2016L100PR
"IC1, IC2, IC3, IC4, IC5, IC6",SOIC127P600X175-16N,6,ULN2003LVDR,
IC10,SOT230P700X180-4N,1,LDL1117S33R,LDL1117S33R
"J1, J10, J11, J8, J9",PinHeader_2x07_P2.54mm_Vertical,5,Conn_02x07_Counter_Clockwise,
J12,PinHeader_2x09_P2.54mm_Vertical,1,Conn_02x09_Counter_Clockwise,
J15,PinHeader_2x04_P2.54mm_Vertical,1,Conn_02x04_Counter_Clockwise,
"J2, J5, J6, J7",PinHeader_2x01_P2.54mm_Vertical,4,Conn_01x02_Pin,
J3,USB_C_Receptacle_GCT_USB4085,1,USB_C_Receptacle,USB4085-GF-A
J4,TerminalBlock_bornier-2_P5.08mm,1,Screw_Terminal_01x02,
JP1,SW_Push_SPST_NO_Alps_SKRK,1,BOOT,
Q10,SOIC127P600X175-8N,1,DMN6070SSD-13,DMN6070SSD-13
"R1, R10, R11, R12, R13, R14, R15, R16, R17, R18, R19, R20, R21, R22, R23, R24, R25, R26, R27, R28, R29, R3, R30, R31, R32, R33, R34, R35, R36, R37, R38, R39, R40, R41, R42, R43, R44, R45, R46, R47, R48, R49, R50, R51, R52, R53, R7, R8, R9",0805,49,2k,CR0805-FX-2001ELF
"R2, R4, R5",0805,3,10k,CR0805-FX-1002ELF
R6,0805,1,120R,CR0805-FX-1200ELF
"SW1, SW2",SMDIP-6_W7.62mm,2,SW_DPDT_x2,
U1,LQFP-64_10x10mm_P0.5mm,1,STM32F405RGTx,
U2,SOIC-8_3.9x4.9mm_P1.27mm,1,TJA1051T/3/2Z,TJA1051T/3/2Z
U3,TSSOP-14_4.4x5mm_P0.65mm,1,MCP2221A-I/ST,MCP2221A-I/ST
Y1,FL0800008Q(handsolder),1,FL0800008Q,FL0800008Q
